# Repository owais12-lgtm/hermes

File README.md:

# hermes
This is a project that gets data from an environmental sensor (BME690) that measures Temperature, Humidity, Pressure, and gas data — IAQ, bVOC, CO₂. It then shows this data on a 0.96" OLED screen, and all of this is controlled with a Xiao RP2040. It also contains an LED matrix for the looks- it's just super cool! 

# Schematic 

# PCB

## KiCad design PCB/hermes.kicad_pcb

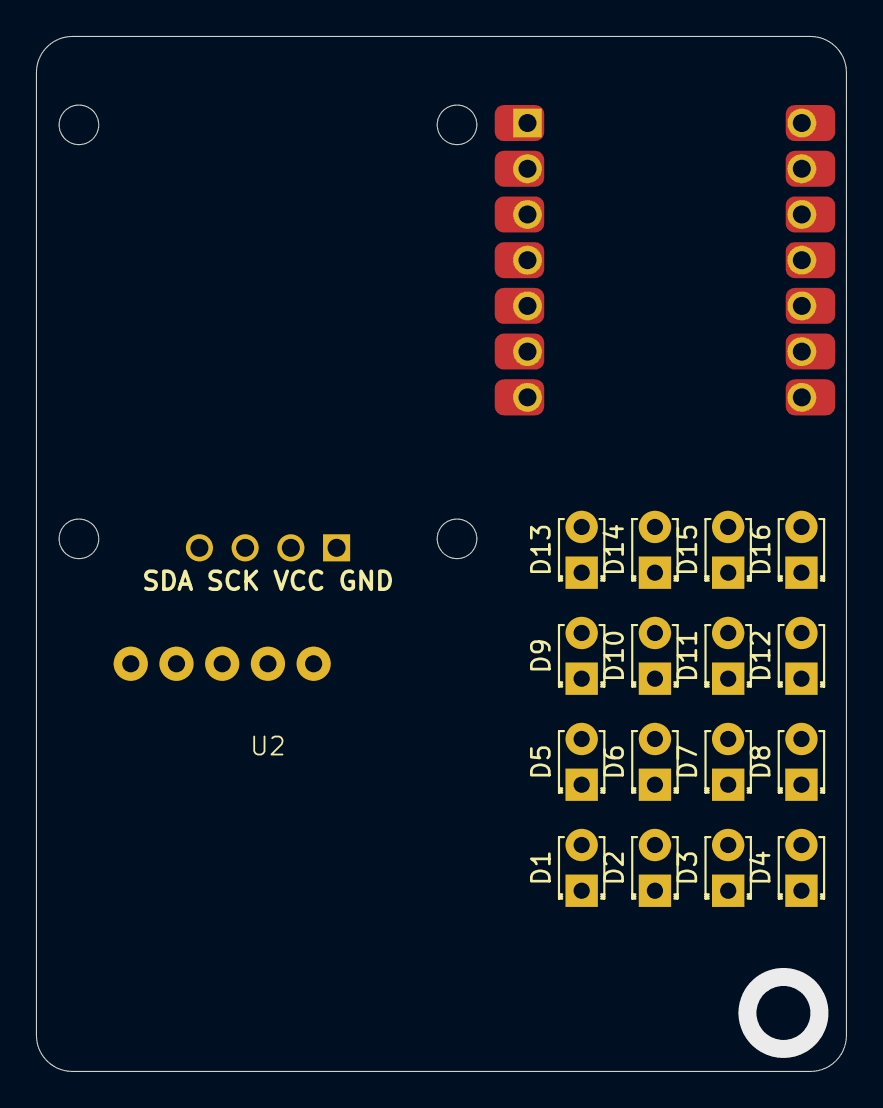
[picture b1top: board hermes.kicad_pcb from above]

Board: 2 copper layers, 45.0 x 57.5 mm, 19 parts (0 on the bottom side), 12 nets, no tracks yet.

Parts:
D1, D2, D3, D4, D5, D6, D7, D8, D9, D10, D11, D12, D13, D14, D15, D16: LED; LED_D1.8mm_W3.3mm_H2.4mm
J1: OLED_128x64
U1: MCU_Seeed_XIAO_RP2040; Seeed_XIAO_RP2040
U2: BME690

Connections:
GND: J1.1 (GND), U1.13 (GND)
GPIO1: D1.1 (K), D5.1 (K), D9.1 (K), D13.1 (K), U1.1 (PA02_A0_D0)
GPIO2: D2.1 (K), D6.1 (K), D10.1 (K), D14.1 (K), U1.2 (PA4_A1_D1)
GPIO3: D3.1 (K), D7.1 (K), D11.1 (K), D15.1 (K), U1.3 (PA10_A2_D2)
GPIO4: D4.1 (K), D8.1 (K), D12.1 (K), D16.1 (K), U1.4 (PA11_A3_D3)
GPIO5: D13.2 (A), D14.2 (A), D15.2 (A), D16.2 (A)
GPIO6: D9.2 (A), D10.2 (A), D11.2 (A), D12.2 (A)
GPIO7: D5.2 (A), D6.2 (A), D7.2 (A), D8.2 (A)
GPIO8: D1.2 (A), D2.2 (A), D3.2 (A), D4.2 (A)
SCL: J1.3 (SCL), U1.6 (PA9_A5_D5_SCL)
SDA: J1.4 (SDA), U1.5 (PA8_A4_D4_SDA)
VCC: J1.2 (VCC), U1.12 (3V3)
